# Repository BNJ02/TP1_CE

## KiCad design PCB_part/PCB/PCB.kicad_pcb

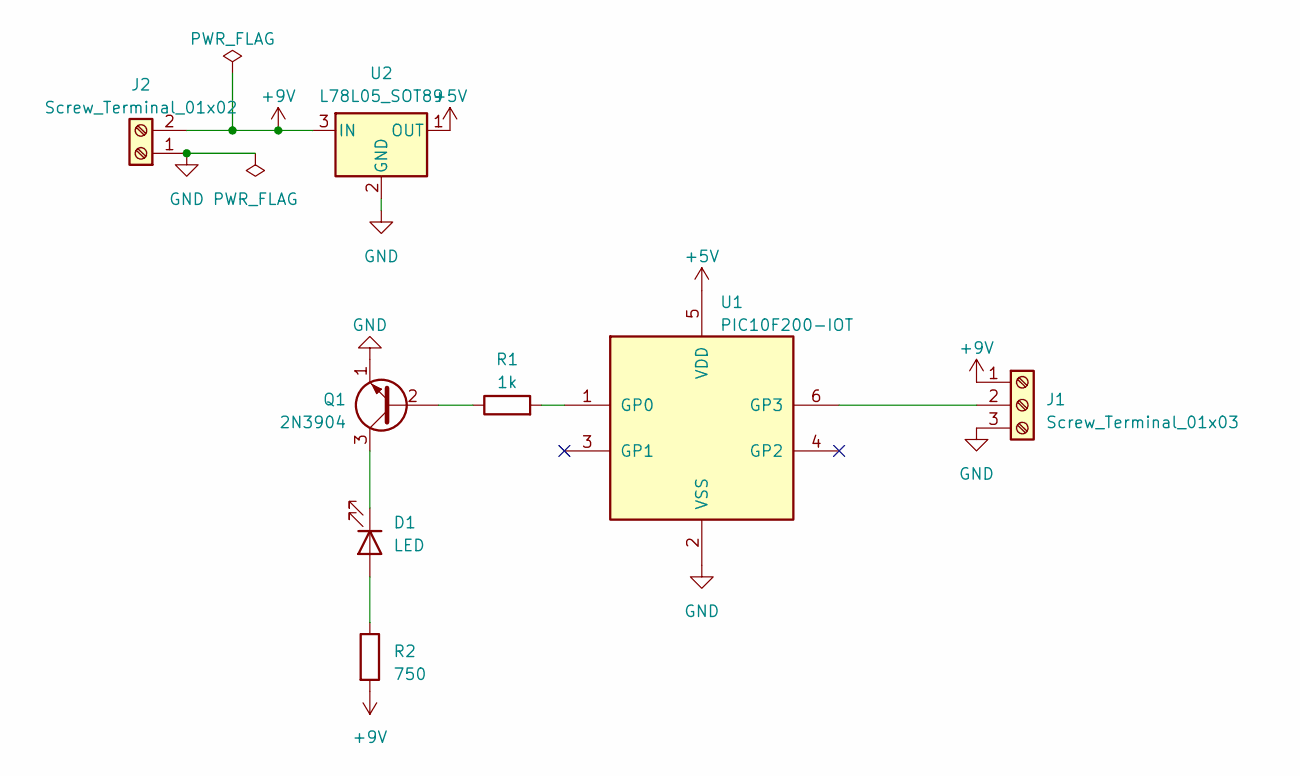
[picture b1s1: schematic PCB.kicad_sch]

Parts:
D1: LED; LED_0201_0603Metric
J1: Screw_Terminal_01x03; PinHeader_1x03_P2.54mm_Vertical
J2: Screw_Terminal_01x02; PinHeader_1x02_P2.54mm_Vertical
Q1: 2N3904; SOT-23
R1: 1k; R_0201_0603Metric
R2: 750; R_0201_0603Metric
U1: PIC10F200-IOT; SOT-23-6
U2: L78L05_SOT89; SOT-89-3

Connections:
+5V: U1.5 (VDD), U2.1 (OUT)
+9V: J1.1, J2.2, R2.2, U2.3 (IN)
GND: J1.3, J2.1, Q1.1 (E), U1.2 (VSS), U2.2 (GND)
unnamed: D1.2 (A), R2.1
unnamed: D1.1 (K), Q1.3 (C)
unnamed: J1.2, U1.6 (GP3)
unnamed: Q1.2 (B), R1.1
unnamed: R1.2, U1.1 (GP0)

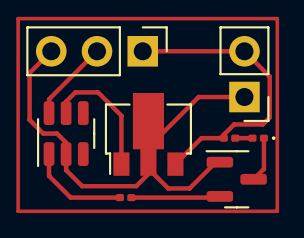
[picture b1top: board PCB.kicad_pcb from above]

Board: 2 copper layers, 8 parts (0 on the bottom side), 8 nets.

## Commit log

2023-09-26 Question 0
2023-09-26 Question 1
2023-09-26 Question 2
2023-09-26 Question 3
2023-09-26 Question 3 modifiée
2023-09-27 Question 3 modif 2
2023-09-27 Question 3 correcte
2023-09-27 Question 4 Crash
2023-09-27 Question 4 Crash 2
2023-09-27 Question 4 correcte
2023-09-27 Question 4 FINIE filtre anti-rebond BP
2023-09-27 Question 5
2023-09-27 Question 5 correcte
2023-09-27 Question 7 correcte
2023-09-27 Question 8 correcte
2023-09-27 Question 9 correcte
2023-09-28 Routage terminé
2023-09-29 Model 3D du boîtier
2023-09-29 BONUS terminé
